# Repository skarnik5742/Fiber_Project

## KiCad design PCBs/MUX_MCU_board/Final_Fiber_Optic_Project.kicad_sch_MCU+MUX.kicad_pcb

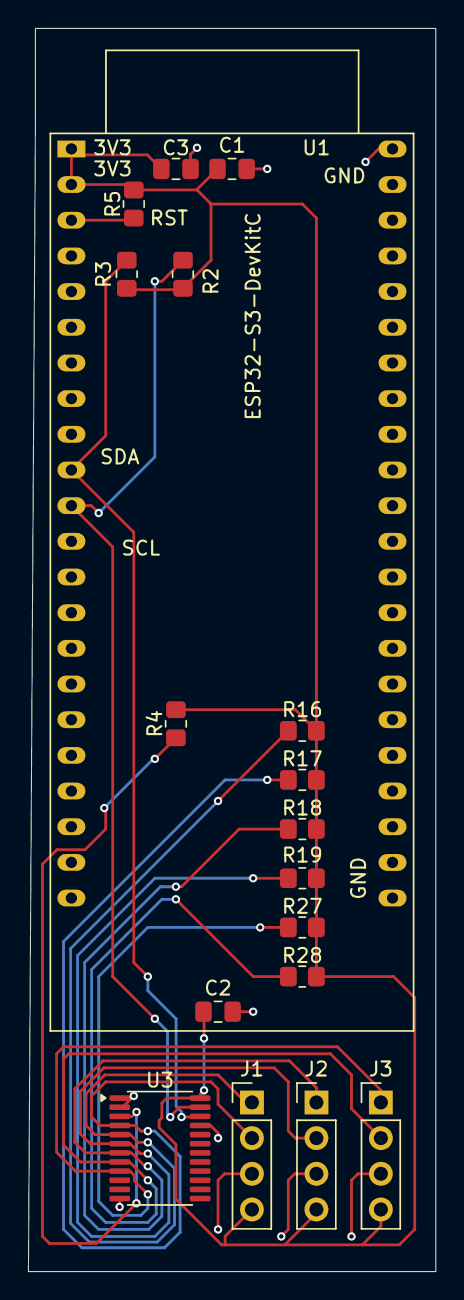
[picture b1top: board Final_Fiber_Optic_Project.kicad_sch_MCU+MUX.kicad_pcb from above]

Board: 2 copper layers, 29.0 x 88.5 mm, 18 parts (0 on the bottom side), 12 nets.

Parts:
C1, C2: 100nF; C_0805_2012Metric_Pad1.18x1.45mm_HandSolder
C3: 10uF; C_0805_2012Metric_Pad1.18x1.45mm_HandSolder
J1, J2, J3: Conn_01x04_Socket; PinHeader_1x04_P2.54mm_Vertical
R2, R3, R4, R5: 10kOhm; R_0805_2012Metric_Pad1.20x1.40mm_HandSolder
R16, R17, R18, R19, R27, R28: 2kOhm; R_0805_2012Metric_Pad1.20x1.40mm_HandSolder
U1: ESP32-S3-DevKitC
U3: TCA9548APWR; TSSOP-24_4.4x7.8mm_P0.65mm

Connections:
GND: C1.2, C2.2, C3.2, J1.3, J2.3, J3.3, U1.22 (GND), U1.23 (GND), U1.24 (GND), U1.44 (GND), U3.1 (A0), U3.2 (A1), U3.12 (GND), U3.21 (A2)
unnamed: J1.1, R16.1, U3.5 (SC0)
unnamed: J1.2, R17.2, U3.4 (SD0)
unnamed: C1.1, C2.1, C3.1, J1.4, J2.4, J3.4, R2.1, R3.1, R4.1, R5.1, R16.2, R17.1, R18.1, R19.2, R27.2, R28.2, U1.1 (3V3), U1.2 (3V3), U3.24 (VCC)
unnamed: J2.1, R18.2, U3.7 (SC1)
unnamed: J2.2, R19.1, U3.6 (SD1)
unnamed: J3.1, R27.1, U3.9 (SC2)
unnamed: J3.2, R28.1, U3.8 (SD2)
unnamed: R5.2, U1.3 (CHIP_PU)
unnamed: R3.2, U1.10 (GPIO17/ADC2_CH6), U3.22 (SCL)
unnamed: R2.2, U1.11 (GPIO18/ADC2_CH7), U3.23 (SDA)
unnamed: R4.2, U3.3 (~RESET)

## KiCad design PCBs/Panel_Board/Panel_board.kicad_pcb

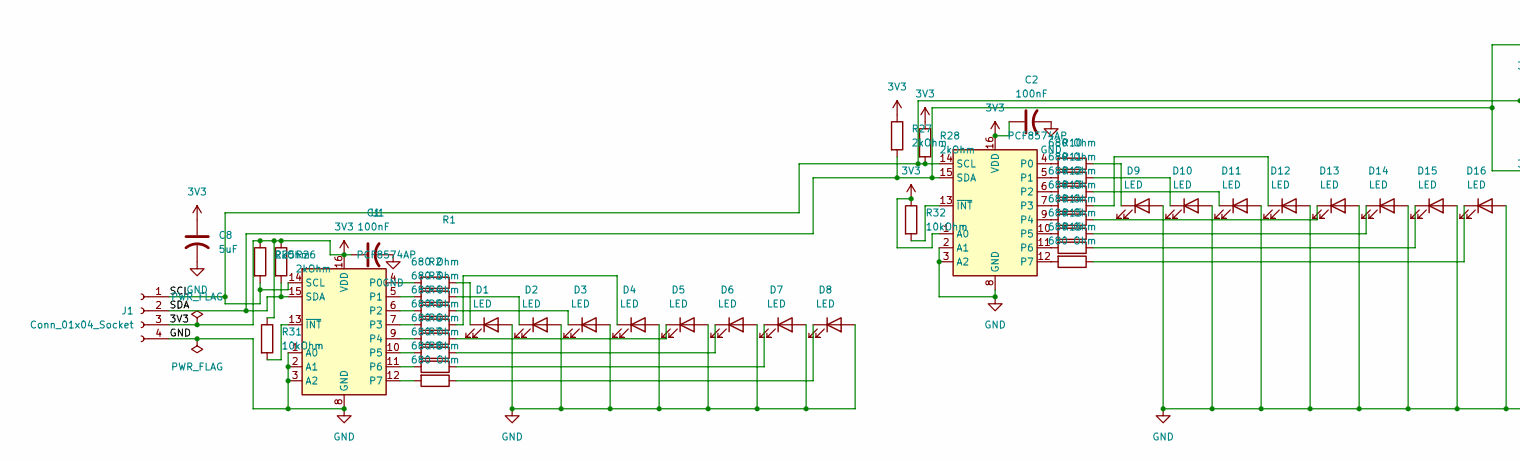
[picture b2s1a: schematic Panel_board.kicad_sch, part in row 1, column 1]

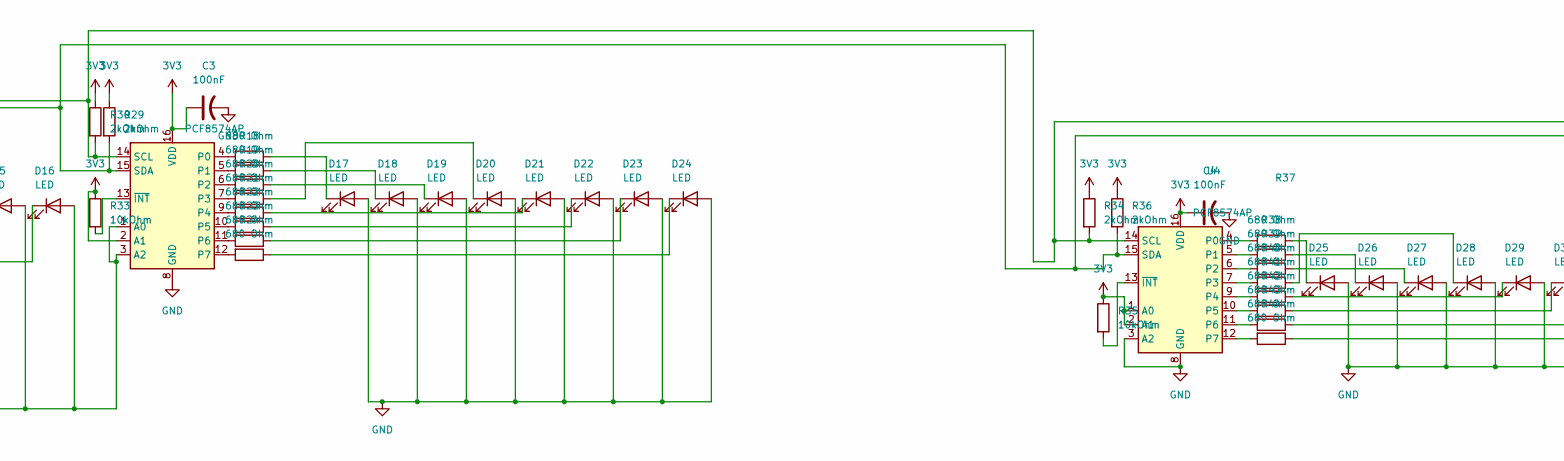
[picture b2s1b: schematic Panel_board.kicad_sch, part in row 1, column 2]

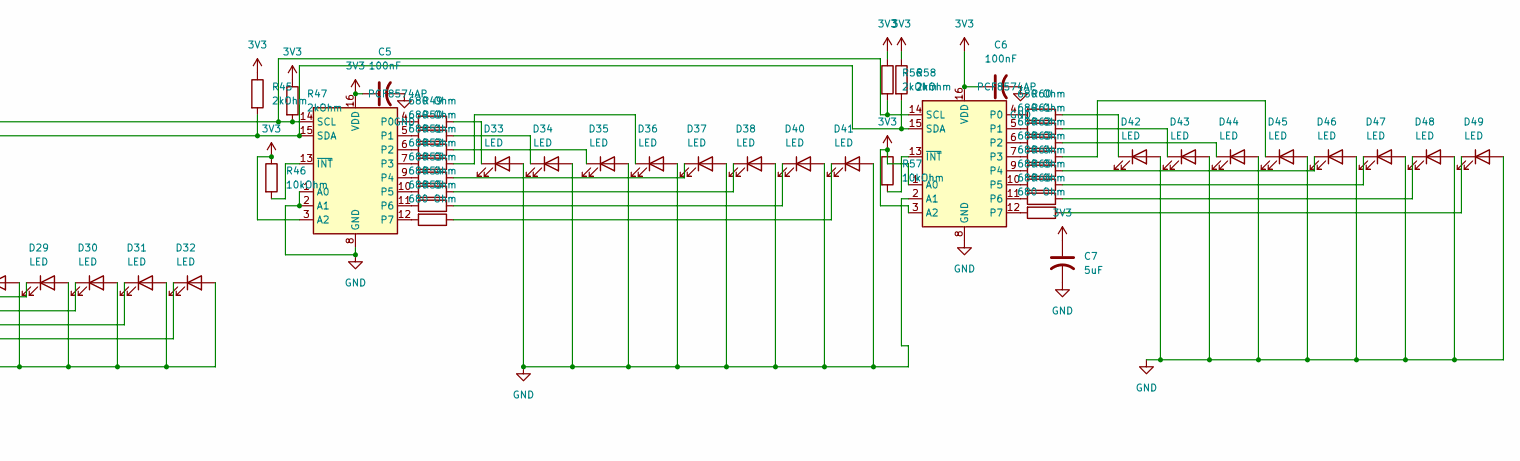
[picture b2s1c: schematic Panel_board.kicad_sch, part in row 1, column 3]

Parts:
C1, C2, C3, C4, C5, C6: 100nF; C_0805_2012Metric_Pad1.18x1.45mm_HandSolder
C7, C8: 5uF; C_0805_2012Metric_Pad1.18x1.45mm_HandSolder
D1, D2, D3, D4, D5, D6, D7, D8, D9, D10, D11, D12, D13, D14, D15, D16, D17, D18, D19, D20, D21, D22, D23, D24, D25, D26, D27, D28, D29, D30, D31, D32, D33, D34, D35, D36, D37, D38, D40, D41, D42, D43, D44, D45, D46, D47, D48, D49: LED; LED_D5.0mm
J1: Conn_01x04_Socket; PinHeader_1x04_P2.54mm_Vertical
R1, R2, R3, R4, R5, R6, R7, R8, R9, R10, R11, R12, R13, R14, R15, R16, R17, R18, R19, R20, R21, R22, R23, R24, R37, R38, R39, R40, R41, R42, R43, R44, R48, R49, R50, R51, R52, R53, R54, R55, R59, R60, R61, R62, R63, R64, R65, R66: 680 Ohm; R_0805_2012Metric_Pad1.20x1.40mm_HandSolder
R25, R26, R27, R28, R29, R30, R34, R36, R45, R47, R56, R58: 2kOhm; R_0805_2012Metric_Pad1.20x1.40mm_HandSolder
R31, R32, R33, R35, R46, R57: 10kOhm; R_0805_2012Metric_Pad1.20x1.40mm_HandSolder
U1, U2, U3, U4, U5, U6: PCF8574AP; DIP-16_W7.62mm

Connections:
3V3: C1.1, C2.1, C3.1, C4.1, C5.1, C6.1, C7.1, C8.1, J1.3, R25.1, R26.1, R27.1, R28.1, R29.1, R30.1, R31.1, R32.1, R33.1, R34.1, R35.1, R36.1, R45.1, R46.1, R47.1, R56.1, R57.1, R58.1, U1.16 (VDD), U2.1 (A0), U2.16 (VDD), U3.2 (A1), U3.16 (VDD), U4.1 (A0), U4.2 (A1), U4.16 (VDD), U5.3 (A2), U5.16 (VDD), U6.1 (A0), U6.3 (A2), U6.16 (VDD)
/SCL: J1.1, R25.2, R28.2, R30.2, R34.2, R47.2, R56.2, U1.14 (SCL), U2.14 (SCL), U3.14 (SCL), U4.14 (SCL), U5.14 (SCL), U6.14 (SCL)
/SDA: J1.2, R26.2, R27.2, R29.2, R36.2, R45.2, R58.2, U1.15 (SDA), U2.15 (SDA), U3.15 (SDA), U4.15 (SDA), U5.15 (SDA), U6.15 (SDA)
GND: C1.2, C2.2, C3.2, C4.2, C5.2, C6.2, C7.2, C8.2, D1.2 (A), D2.2 (A), D3.2 (A), D4.2 (A), D5.2 (A), D6.2 (A), D7.2 (A), D8.2 (A), D9.2 (A), D10.2 (A), D11.2 (A), D12.2 (A), D13.2 (A), D14.2 (A), D15.2 (A), D16.2 (A), D17.2 (A), D18.2 (A), D19.2 (A), D20.2 (A), D21.2 (A), D22.2 (A), D23.2 (A), D24.2 (A), D25.2 (A), D26.2 (A), D27.2 (A), D28.2 (A), D29.2 (A), D30.2 (A), D31.2 (A), D32.2 (A), D33.2 (A), D34.2 (A), D35.2 (A), D36.2 (A), D37.2 (A), D38.2 (A), D40.2 (A), D41.2 (A), D42.2 (A), D43.2 (A), D44.2 (A), D45.2 (A), D46.2 (A), D47.2 (A), D48.2 (A), D49.2 (A), J1.4, U1.1 (A0), U1.2 (A1), U1.3 (A2), U1.8 (GND), U2.2 (A1), U2.3 (A2), U2.8 (GND), U3.1 (A0), U3.3 (A2), U3.8 (GND), U4.3 (A2), U4.8 (GND), U5.1 (A0), U5.2 (A1), U5.8 (GND), U6.2 (A1), U6.8 (GND)
unnamed: D1.1 (K), R1.1
unnamed: D2.1 (K), R2.1
unnamed: D3.1 (K), R3.1
unnamed: D4.1 (K), R4.1
unnamed: D5.1 (K), R5.1
unnamed: D6.1 (K), R6.1
unnamed: D7.1 (K), R7.1
unnamed: D8.1 (K), R8.1
unnamed: D9.1 (K), R9.1
unnamed: D10.1 (K), R10.1
unnamed: D11.1 (K), R11.1
unnamed: D12.1 (K), R12.1
unnamed: D13.1 (K), R13.1
unnamed: D14.1 (K), R14.1
unnamed: D15.1 (K), R15.1
unnamed: D16.1 (K), R16.1
unnamed: D17.1 (K), R17.1
unnamed: D18.1 (K), R18.1
unnamed: D19.1 (K), R19.1
unnamed: D20.1 (K), R20.1
unnamed: D21.1 (K), R21.1
unnamed: D22.1 (K), R22.1
unnamed: D23.1 (K), R23.1
unnamed: D24.1 (K), R24.1
unnamed: D25.1 (K), R37.1
unnamed: D26.1 (K), R38.1
unnamed: D27.1 (K), R39.1
unnamed: D28.1 (K), R40.1
unnamed: D29.1 (K), R41.1
unnamed: D30.1 (K), R42.1
unnamed: D31.1 (K), R43.1
unnamed: D32.1 (K), R44.1
unnamed: D33.1 (K), R48.1
unnamed: D34.1 (K), R49.1
unnamed: D35.1 (K), R50.1
unnamed: D36.1 (K), R51.1
unnamed: D37.1 (K), R52.1
unnamed: D38.1 (K), R53.1
unnamed: D40.1 (K), R54.1
unnamed: D41.1 (K), R55.1
unnamed: D42.1 (K), R59.1
unnamed: D43.1 (K), R60.1
unnamed: D44.1 (K), R61.1
unnamed: D45.1 (K), R62.1
unnamed: D46.1 (K), R63.1
unnamed: D47.1 (K), R64.1
unnamed: D48.1 (K), R65.1
unnamed: D49.1 (K), R66.1
unnamed: R1.2, U1.4 (P0)
unnamed: R2.2, U1.5 (P1)
unnamed: R3.2, U1.6 (P2)
unnamed: R4.2, U1.7 (P3)
unnamed: R5.2, U1.9 (P4)
unnamed: R6.2, U1.10 (P5)
unnamed: R7.2, U1.11 (P6)
unnamed: R8.2, U1.12 (P7)
unnamed: R31.2, U1.13 (~INT)
unnamed: R9.2, U2.4 (P0)
unnamed: R10.2, U2.5 (P1)
unnamed: R11.2, U2.6 (P2)
unnamed: R12.2, U2.7 (P3)
unnamed: R13.2, U2.9 (P4)
unnamed: R14.2, U2.10 (P5)
unnamed: R15.2, U2.11 (P6)
unnamed: R16.2, U2.12 (P7)
unnamed: R32.2, U2.13 (~INT)
unnamed: R17.2, U3.4 (P0)
unnamed: R18.2, U3.5 (P1)
unnamed: R19.2, U3.6 (P2)
unnamed: R20.2, U3.7 (P3)
unnamed: R21.2, U3.9 (P4)
unnamed: R22.2, U3.10 (P5)
unnamed: R23.2, U3.11 (P6)
unnamed: R24.2, U3.12 (P7)
unnamed: R33.2, U3.13 (~INT)
unnamed: R37.2, U4.4 (P0)
unnamed: R38.2, U4.5 (P1)
unnamed: R39.2, U4.6 (P2)
unnamed: R40.2, U4.7 (P3)
unnamed: R41.2, U4.9 (P4)
unnamed: R42.2, U4.10 (P5)
unnamed: R43.2, U4.11 (P6)
unnamed: R44.2, U4.12 (P7)
unnamed: R35.2, U4.13 (~INT)
unnamed: R48.2, U5.4 (P0)
unnamed: R49.2, U5.5 (P1)
unnamed: R50.2, U5.6 (P2)
unnamed: R51.2, U5.7 (P3)
unnamed: R52.2, U5.9 (P4)
unnamed: R53.2, U5.10 (P5)
unnamed: R54.2, U5.11 (P6)
unnamed: R55.2, U5.12 (P7)
unnamed: R46.2, U5.13 (~INT)
unnamed: R59.2, U6.4 (P0)
unnamed: R60.2, U6.5 (P1)
unnamed: R61.2, U6.6 (P2)
unnamed: R62.2, U6.7 (P3)
unnamed: R63.2, U6.9 (P4)
unnamed: R64.2, U6.10 (P5)
unnamed: R65.2, U6.11 (P6)
unnamed: R66.2, U6.12 (P7)
unnamed: R57.2, U6.13 (~INT)

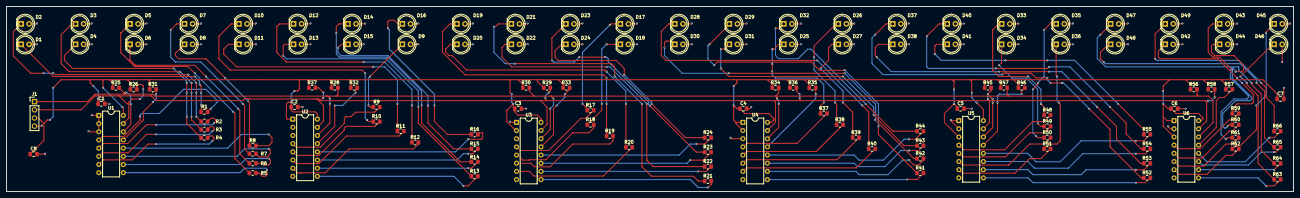
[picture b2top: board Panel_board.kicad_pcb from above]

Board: 2 copper layers, 400.0 x 57.5 mm, 129 parts (0 on the bottom side), 106 nets.
